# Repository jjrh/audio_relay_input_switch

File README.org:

* about
  - relay input board for audio.

  Based on a similar project [fn:1]

* bom
** relays
   | HK19F   | http://www.aliexpress.com/item/High-Quality-10-x-DC-5V-Coil-125V-1A-DC-30V-2A-AC-2A-30V-DC/32263891251.html                                                                                                                           |
   | RY12W-K | http://www.aliexpress.com/item/20-pcs-lot-TAKAMISAWA-RY12W-K-12V-DPDT-Signal-Relay-For-Audio/32474400291.html?spm=2114.031010208.3.20.ds0aQE&ws_ab_test=searchweb201556_3,searchweb201644_1_79_78_77_82_80_62_81_61,searchweb201560_6 |

** interconnects
   search for 2.54-5P XH-5P
   XH-2P,XH-3P,XH-4P,XH-5P,etc
   http://www.aliexpress.com/item/XH-red-and-white-cable-3P-single-head-plug-the-other-end-of-the-housing-tinned/32372398975.html

** mouser shared cart
  http://www.mouser.com/ProjectManager/ProjectDetail.aspx?AccessID=747d0c13f4

** datasheets
   | ULN2003 | http://www.ti.com/lit/ds/symlink/uln2003a.pdf |

#+START_IMAGES:

* images

  	#+CAPTION:
	#+NAME:relay_switch.sch.png
	#+attr_html: :width 800px
	[[./images/relay_switch.sch.png]]

	#+CAPTION:
	#+NAME:relay_switch-brd.png
	#+attr_html: :width 800px
	[[./images/relay_switch-brd.png]]

	#+CAPTION:
	#+NAME:relay_switch_3d_1.png
	#+attr_html: :width 800px
	[[./images/relay_switch_3d_1.png]]

	#+CAPTION:
	#+NAME:relay_switch_3d_2.png
	#+attr_html: :width 800px
	[[./images/relay_switch_3d_2.png]]

	#+CAPTION:
	#+NAME:relay_switch_3d_3.png
	#+attr_html: :width 800px
	[[./images/relay_switch_3d_3.png]]

	#+CAPTION:
	#+NAME:relay_switch_3d_4.png
	#+attr_html: :width 800px
	[[./images/relay_switch_3d_4.png]]

#+END_IMAGES:

* Footnotes

[fn:1] http://www.diyaudio.com/forums/analog-line-level/254244-building-complete-preamp-arduino-remote-volume-input-control.html#post3882944

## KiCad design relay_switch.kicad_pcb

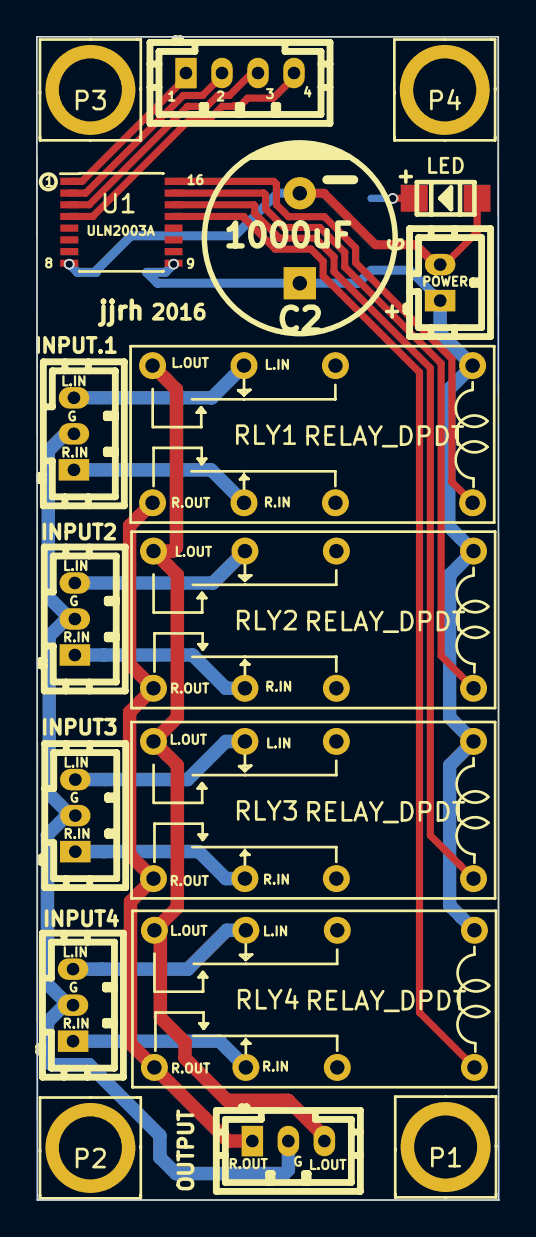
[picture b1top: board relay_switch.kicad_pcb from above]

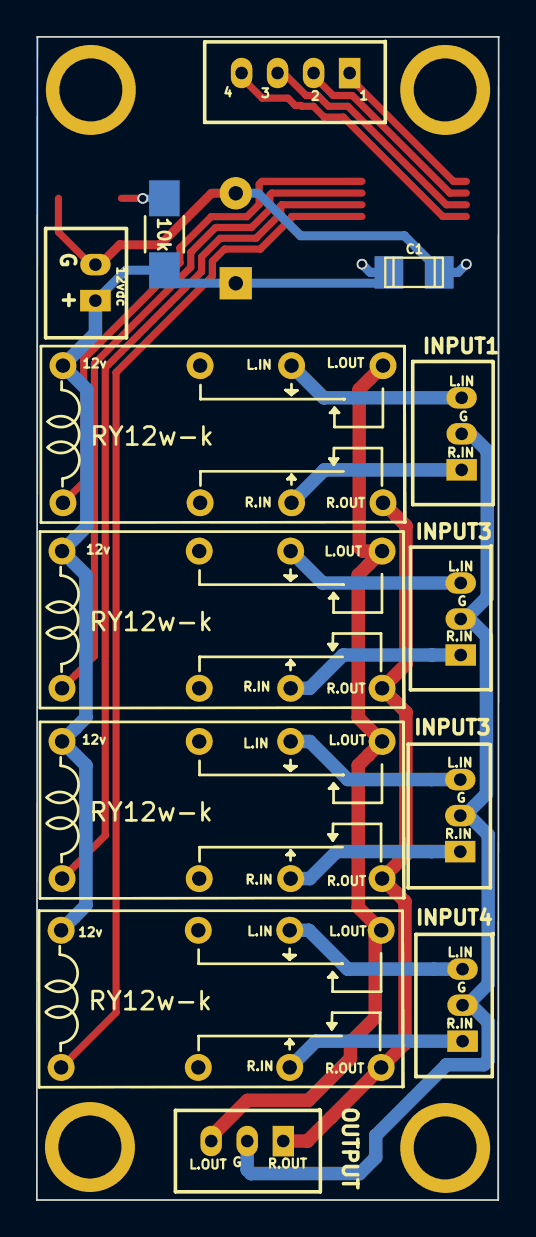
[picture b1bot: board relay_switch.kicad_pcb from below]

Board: 2 copper layers, 25.7 x 64.6 mm, 20 parts (2 on the bottom side), 22 nets.

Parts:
C1: 100nF; c_1206
C2: 1000uF; CP_10x20mm
D1: LED; Led_1206
P1, P2, P3, P4: board_mount; 3.5mm_m3
P8: OUTPUT; b3b-ph-kl
P9: INPUT.1; b3b-ph-kl
P10: INPUT2; b3b-ph-kl
P11: INPUT3; b3b-ph-kl
P12: INPUT4; b3b-ph-kl
P13: POWER; b2b-ph-kl
P14: J_CONN_01X04; b4b-ph-kl
R1: 10k; R_1206_HandSoldering
RLY1, RLY2, RLY3, RLY4: RELAY_DPDT; RY12w-k_bigger_holes
U1: ULN2003A; SSOP-16_4.4x5.2mm_Pitch0.65mm

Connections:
+12V: C1.2, C2.1, P13.1, R1.1, RLY1.8, RLY2.8, RLY3.8, RLY4.8, U1.9
GND: C1.1, C2.2, D1.1, P13.2, U1.8
L_OUT: P8.3, RLY1.5, RLY2.5, RLY3.5, RLY4.5
unnamed: D1.2, R1.2
unnamed: RLY1.1, U1.16
unnamed: RLY2.1, U1.15
unnamed: RLY3.1, U1.14
unnamed: RLY4.1, U1.13
R1_GND: P8.2, P9.2, P10.2, P11.2, P12.2
R1_L_IN: P9.3, RLY1.6
R1_R_IN: P9.1, RLY1.3
R2_L_IN: P10.3, RLY2.6
R2_R_IN: P10.1, RLY2.3
R3_L_IN: P11.3, RLY3.6
R3_R_IN: P11.1, RLY3.3
R4_L_IN: P12.3, RLY4.6
R4_R_IN: P12.1, RLY4.3
R_OUT: P8.1, RLY1.4, RLY2.4, RLY3.4, RLY4.4
T1: P14.1, U1.1
T2: P14.2, U1.2
T3: P14.3, U1.3
T4: P14.4, U1.4

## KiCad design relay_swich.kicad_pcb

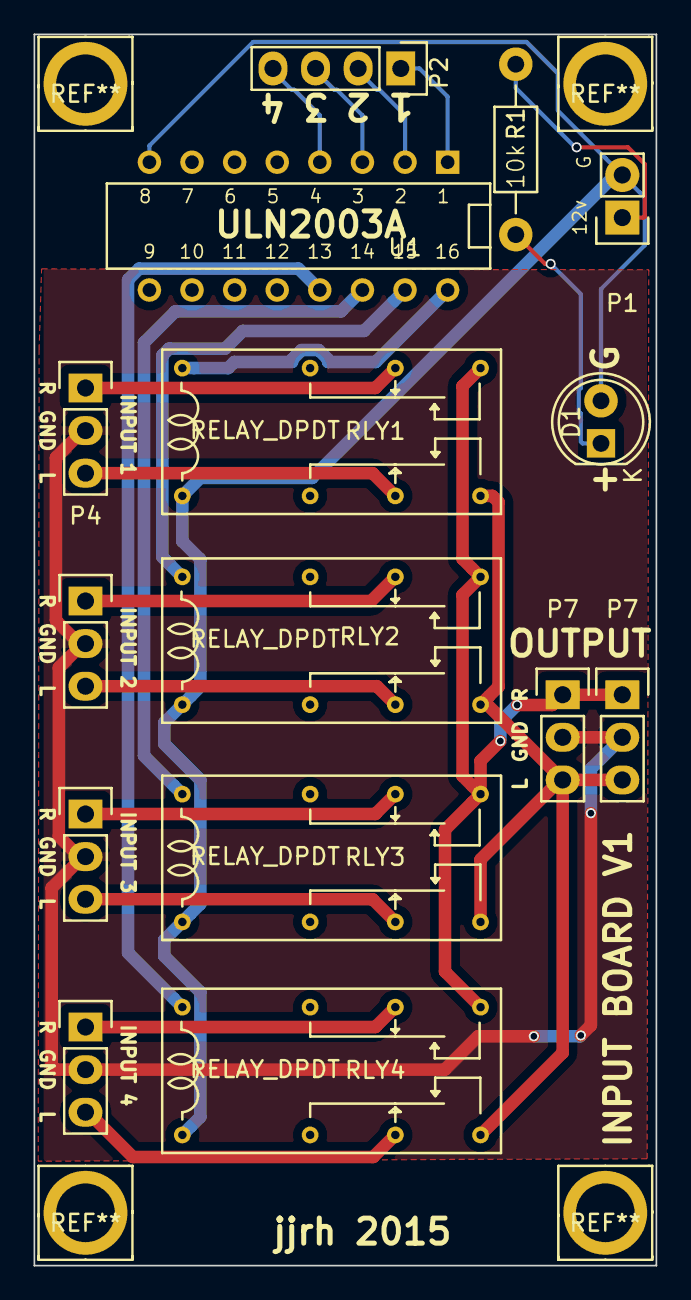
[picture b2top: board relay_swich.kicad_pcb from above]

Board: 2 copper layers, 37.1 x 73.4 mm, 15 parts (0 on the bottom side), 22 nets.

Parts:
D1: LED; LED-5MM
P1: POWER; Pin_Header_Straight_1x02
P2: CONN_01X04; Pin_Header_Straight_1x04
P3: INPUT_1; Pin_Header_Straight_1x03
P4: INPUT_2; Pin_Header_Straight_1x03
P5: INPUT_3; Pin_Header_Straight_1x03
P6: INPUT_4; Pin_Header_Straight_1x03
P7, P7#2: OUTPUT; Pin_Header_Straight_1x03
R1: 10k; Resistor_Horizontal_RM10mm
RLY1, RLY2, RLY3, RLY4: RELAY_DPDT; RY12w-k
U1: ULN2003A; DIP-16__300

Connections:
+12V: P1.1, R1.1, U1.9
GND: D1.2, P1.2, RLY1.8, RLY2.8, RLY3.8, RLY4.8, U1.8
L_OUT: P7.3, P7#2.3, RLY1.5, RLY2.5, RLY3.5, RLY4.5
unnamed: D1.1, R1.2
unnamed: P2.1, U1.1
unnamed: P2.2, U1.2
unnamed: P2.3, U1.3
unnamed: P2.4, U1.4
unnamed: RLY1.1, U1.16
unnamed: RLY2.1, U1.15
unnamed: RLY3.1, U1.14
unnamed: RLY4.1, U1.13
R1_L_IN: P3.3, RLY1.6
R1_R_IN: P3.1, RLY1.3
R2_GND: P3.2, P4.2, P5.2, P6.2, P7.2, P7#2.2
R2_L_IN: P4.3, RLY2.6
R2_R_IN: P4.1, RLY2.3
R3_L_IN: P5.3, RLY3.6
R3_R_IN: P5.1, RLY3.3
R4_L_IN: P6.3, RLY4.6
R4_R_IN: P6.1, RLY4.3
R_OUT: P7.1, P7#2.1, RLY1.4, RLY2.4, RLY3.4, RLY4.4

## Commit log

2015-08-29 initialized repo
2015-08-29 added script to generate org images, generated images and added to readme, there was a file that was commited but was renamed and I didn't do git mv
2015-08-29 forgot to add the images...
2015-12-18 fixing schematic issue, where we should have been using gnd to trigger the relays vs 12v
2015-12-18 added JST connectors
2015-12-18 rerouted pcb
2015-12-18 netlist
2016-01-01 couple misc changes, trying to finalize the pcb
2016-01-01 removed screwmount stuff, added boardmount parts to sch
2016-01-01 updated netlist to include smd parts
2016-01-03 board almost finished
2016-01-03 set 3d footprint for the led
2016-01-03 generated images, included the bin directory, put in license, updated readme
2016-01-03 removed duplicate image
2016-01-03 added more information to the readme, reorganized info
2016-01-03 board changes and corrections
2016-01-03 moved vias for cap so they weren't ontop of the pads
2016-01-03 updates images
